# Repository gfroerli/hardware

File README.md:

## PCB

## Datasheets

- Enclosure: http://www.produktinfo.conrad.com/datenblaetter/525000-549999/536028-da-01-de-GEHAEUSE_ABS_PICCOLO_ABS_B_65_G.pdf

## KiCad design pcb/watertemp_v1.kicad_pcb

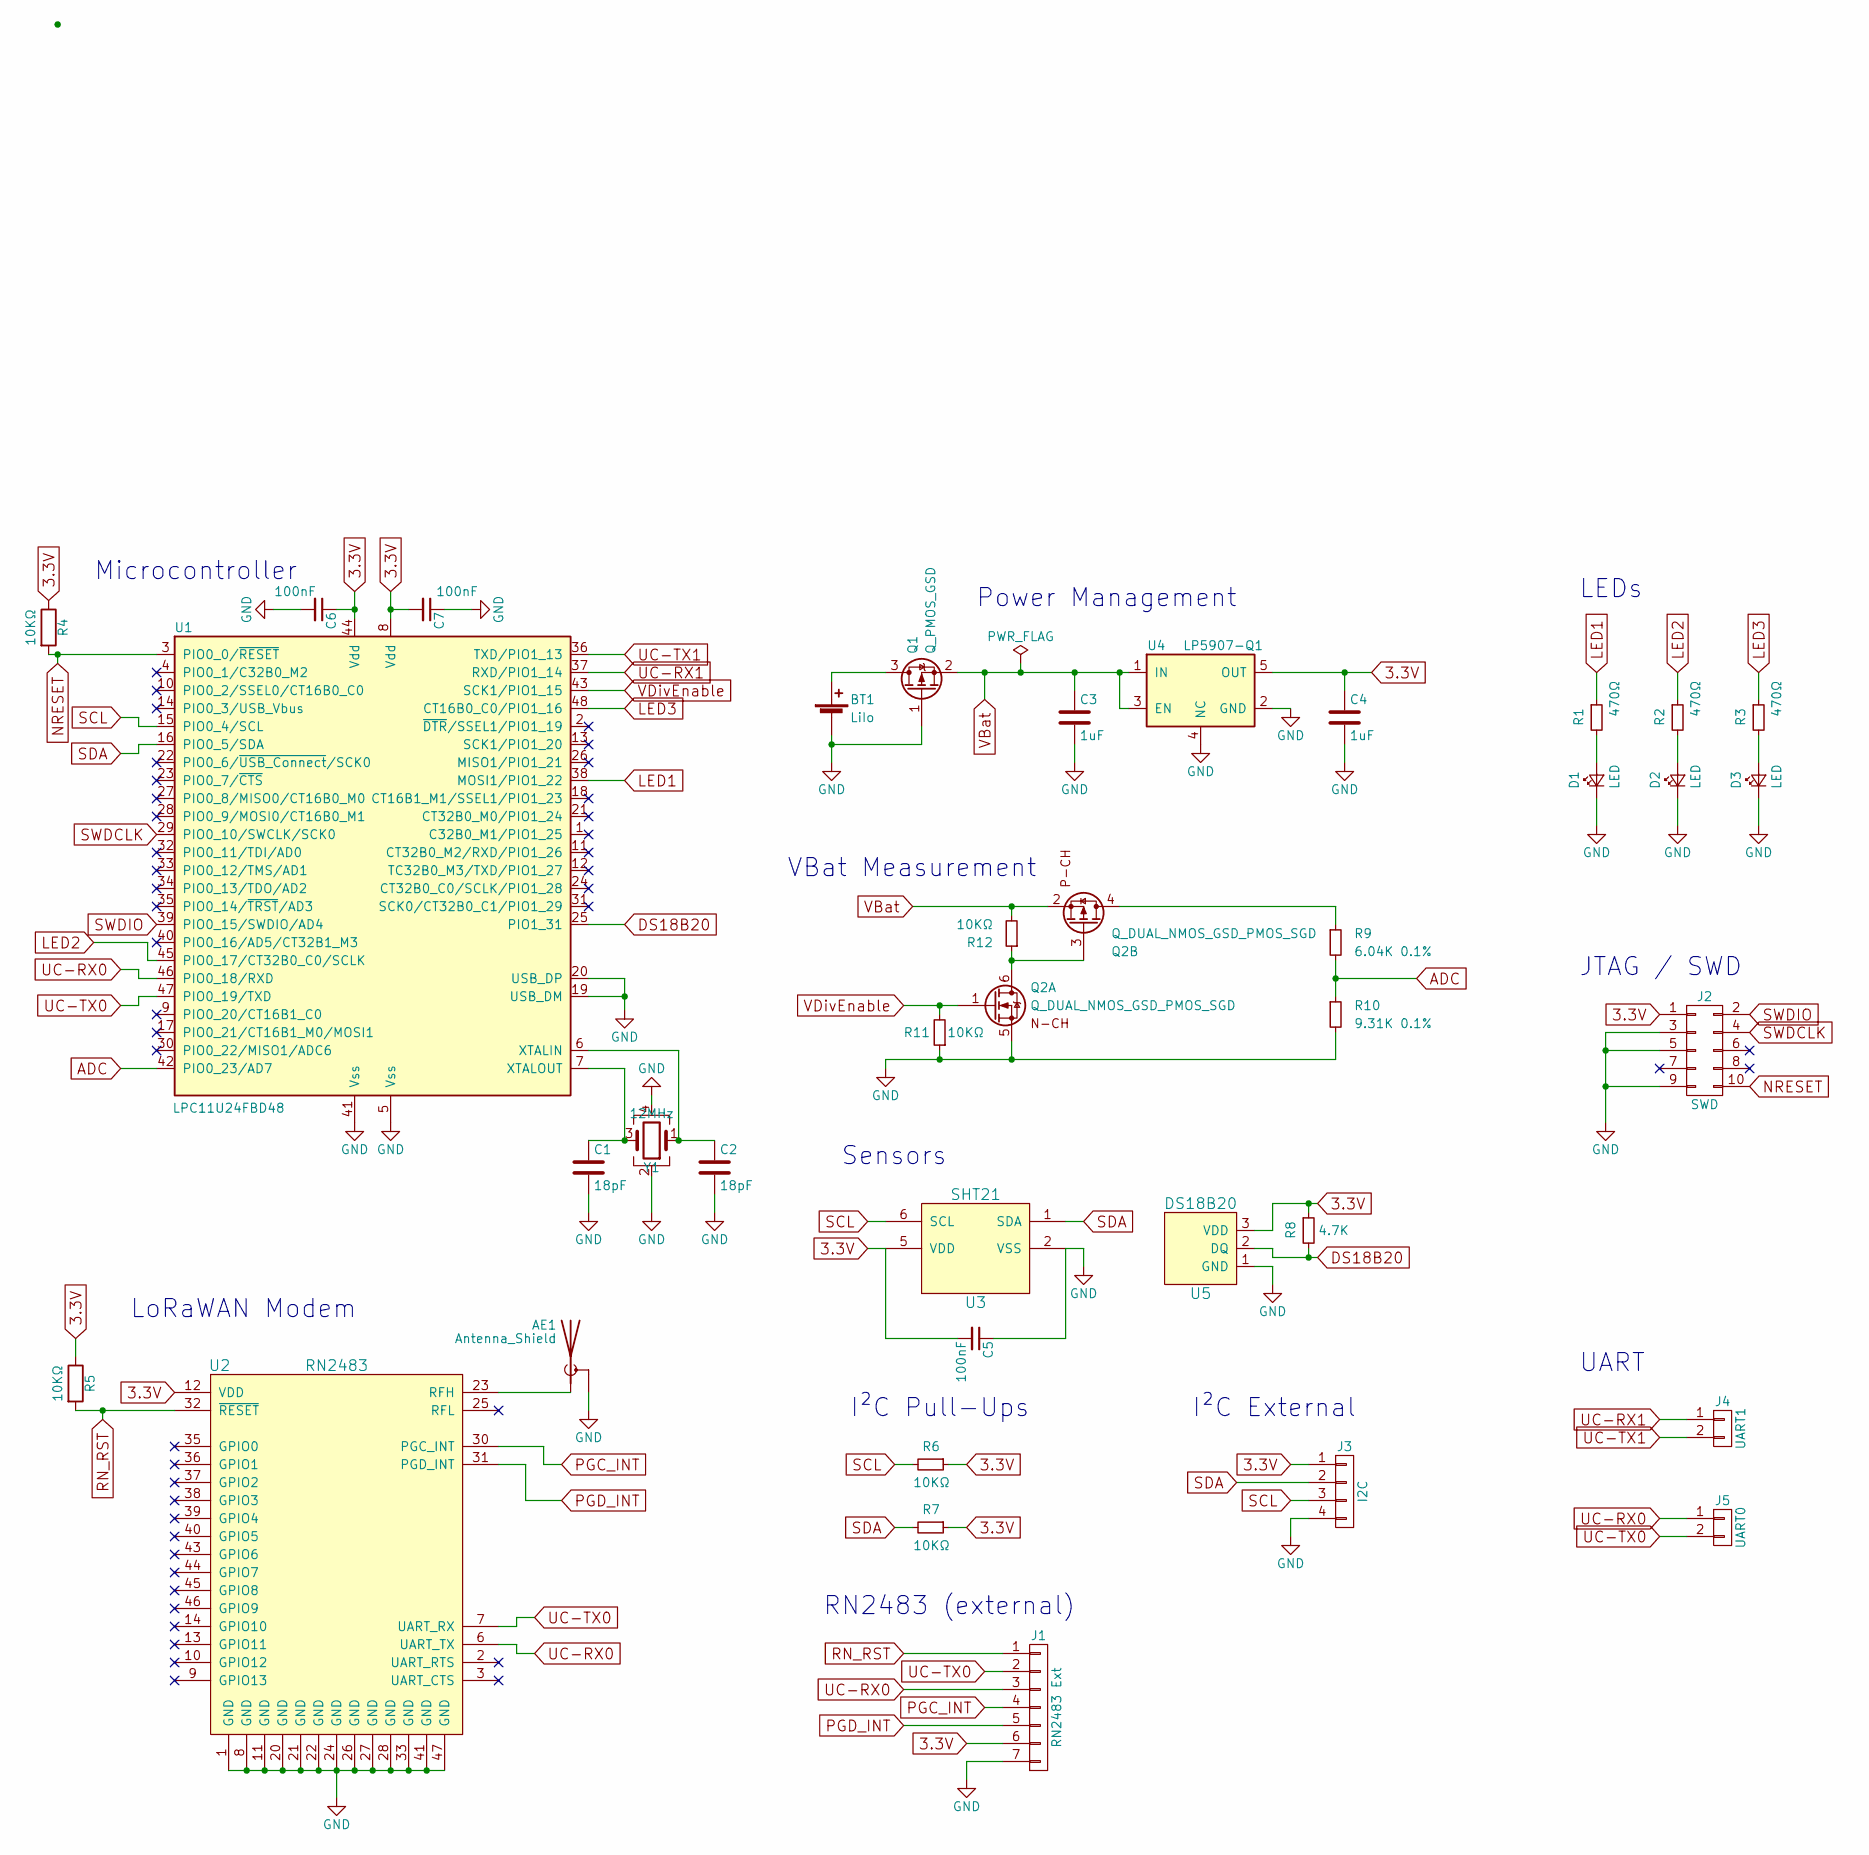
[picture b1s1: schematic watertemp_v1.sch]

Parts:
AE1: Antenna_Shield; SMA_EDGE; Digikey J502-ND
BT1: LiIo; 36-54-ND; Digikey 36-54-ND
C1, C2: 18pF; C_0805; Part Samsung CL21C180JBANNNC; Digikey 1276-1107-1-ND
C3: 1uF; C_0805; Part Samsung CL21B105KOFNNNG; Digikey 1276-6471-1-ND
C4: 1uF; C_0805; Part Samsung Samsung CL21B105KOFNNNG; Digikey 1276-6471-1-ND
C5: 100nF; C_0805_HandSoldering; Digikey 1276-6468-1-ND
C6, C7: 100nF; C_0805; Digikey 1276-6468-1-ND
D1: LED; LED_0805; Digikey 475-1278-1-ND
D2: LED; LED_0805; Digikey 475-2560-1-ND
D3: LED; LED_0805; Digikey 475-1410-1-ND
J1: RN2483 Ext; Pin_Header_Straight_1x07_Pitch2.54mm
J2: SWD; SWD_10Pin; Digikey 1175-1629-ND
J3: I2C; Pin_Header_Straight_1x04_Pitch2.54mm
J4: UART1; Pin_Header_Straight_1x02_Pitch2.54mm
J5: UART0; Pin_Header_Straight_1x02_Pitch2.54mm
Q1: Q_PMOS_GSD; SOT-23; Digikey SSM3J338RLFCT-ND
Q2: Q_DUAL_NMOS_GSD_PMOS_SGD; TSOT26; Digikey DMC2038LVT-7DICT-ND
R1, R2, R3: 470Ω; R_0805; Digikey 311-470CRCT-ND
R4, R5, R6, R7, R11, R12: 10KΩ; R_0805; Digikey 311-10KARCT-ND
R8: 4.7K; R_0805; Digikey 311-4.70KCRCT-ND
R9: 6.04K 0.1%; R_0805; Digikey P20683CT-ND
R10: 9.31K 0.1%; R_0805; Digikey YAG2002CT-ND
U1: LPC11U24FBD48; LQFP-48_7x7mm_Pitch0.5mm; Digikey 568-8460-ND
U2: RN2483; DigiKey RN2483A-I/RM103-ND
U3: SHT21
U4: LP5907-Q1; SOT-23-5; Digikey 296-40365-1-ND
U5: DS18B20; Pin_Header_Straight_1x03_Pitch2.54mm
Y1: 12MHz; Crystal_SMD_Abracon_ABM8G-4pin_3.2x2.5mm; Part ABM8G-12.000MHZ-4Y-T3; Digikey 535-10901-1-ND

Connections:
3.3V: C4.1, C5.2, C6.1, C7.2, J1.6, J2.1, J3.1, R4.1, R5.1, R6.1, R7.1, R8.1, U1.8 (Vdd), U1.44 (Vdd), U2.12 (VDD), U3.5 (VDD), U4.5 (OUT), U5.3 (VDD)
ADC: R9.2, R10.1, U1.42 (PIO0_23/AD7)
DS18B20: R8.2, U1.25 (PIO1_31), U5.2 (DQ)
GND: AE1.2 (Shield), BT1.2 (-), C1.2, C2.2, C3.2, C4.2, C5.1, C6.2, C7.1, D1.1 (K), D2.1 (K), D3.1 (K), J1.7, J2.3, J2.5, J2.9, J3.4, Q1.1 (G), Q2.5 (S1), R10.2, R11.1, U1.5 (Vss), U1.19 (USB_DM), U1.20 (USB_DP), U1.41 (Vss), U2.1 (GND), U2.8 (GND), U2.11 (GND), U2.20 (GND), U2.21 (GND), U2.22 (GND), U2.24 (GND), U2.26 (GND), U2.27 (GND), U2.28 (GND), U2.33 (GND), U2.41 (GND), U2.47 (GND), U3.2 (VSS), U4.2 (GND), U4.4 (NC), U5.1 (GND), Y1.2, Y1.4
LED1: R1.1, U1.38 (MOSI1/PIO1_22)
LED2: R2.1, U1.45 (PIO0_17/CT32B0_C0/SCLK)
LED3: R3.1, U1.48 (CT16B0_C0/PIO1_16)
NRESET: J2.10, R4.2, U1.3 (PIO0_0/~RESET)
unnamed: AE1.1 (A), U2.23 (RFH)
unnamed: BT1.1 (+), Q1.3 (D)
unnamed: C1.1, U1.7 (XTALOUT), Y1.3
unnamed: C2.1, U1.6 (XTALIN), Y1.1
unnamed: D1.2 (A), R1.2
unnamed: D2.2 (A), R2.2
unnamed: D3.2 (A), R3.2
unnamed: Q2.3 (G2), Q2.6 (D1), R12.1
unnamed: Q2.4 (D2), R9.1
PGC_INT: J1.4, U2.30 (PGC_INT)
PGD_INT: J1.5, U2.31 (PGD_INT)
RN_RST: J1.1, R5.2, U2.32 (~RESET)
SCL: J3.3, R6.2, U1.15 (PIO0_4/SCL), U3.6 (SCL)
SDA: J3.2, R7.2, U1.16 (PIO0_5/SDA), U3.1 (SDA)
SWDCLK: J2.4, U1.29 (PIO0_10/SWCLK/SCK0)
SWDIO: J2.2, U1.39 (PIO0_15/SWDIO/AD4)
UC-RX0: J1.3, J5.1, U1.46 (PIO0_18/RXD), U2.6 (UART_TX)
UC-RX1: J4.1, U1.37 (RXD/PIO1_14)
UC-TX0: J1.2, J5.2, U1.47 (PIO0_19/TXD), U2.7 (UART_RX)
UC-TX1: J4.2, U1.36 (TXD/PIO1_13)
VBat: C3.1, Q1.2 (S), Q2.2 (S2), R12.2, U4.1 (IN), U4.3 (EN)
VDivEnable: Q2.1 (G1), R11.2, U1.43 (SCK1/PIO1_15)

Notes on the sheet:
Power Management
Microcontroller
LoRaWAN Modem
Sensors
JTAG / SWD
LEDs
I²C Pull-Ups
I²C External
UART
RN2483 (external)
VBat Measurement

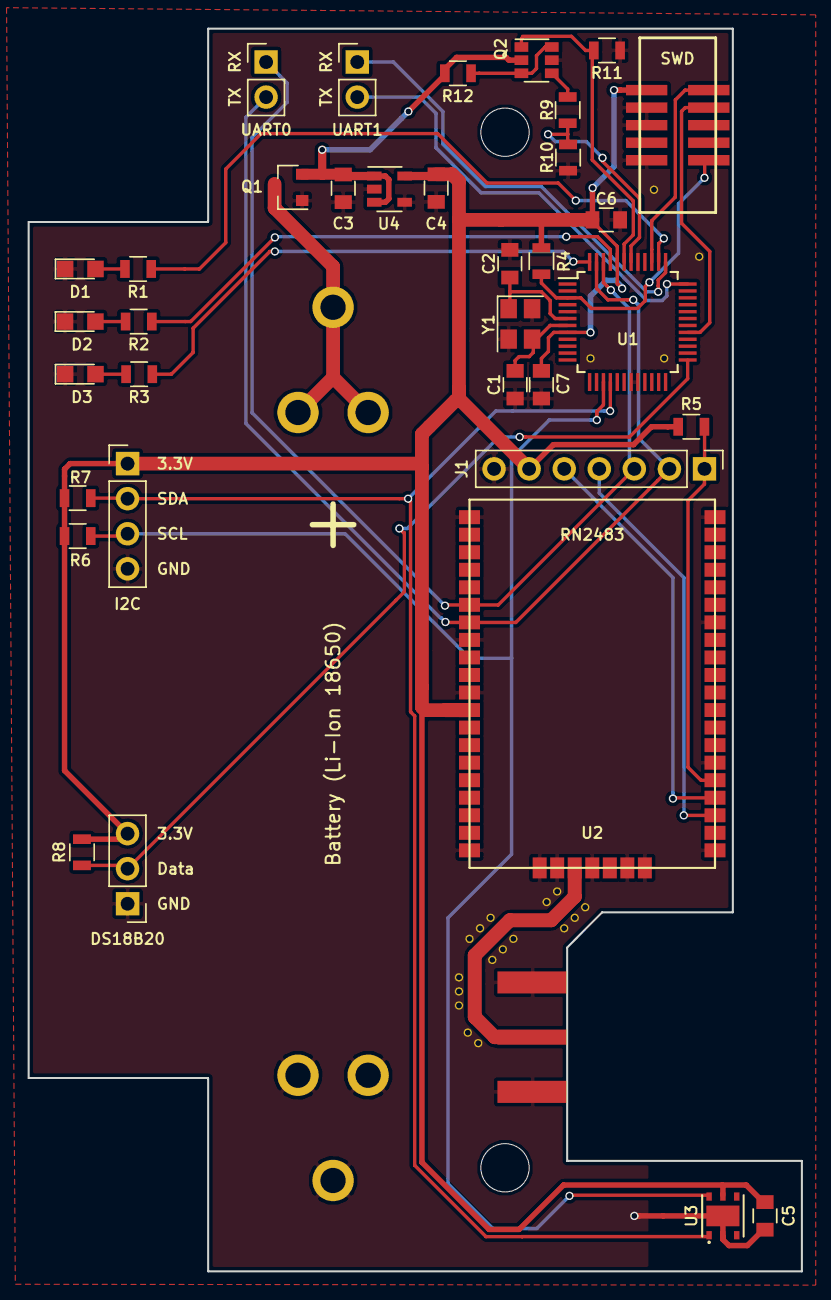
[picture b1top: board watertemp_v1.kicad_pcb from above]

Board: 2 copper layers, 56.0 x 90.0 mm, 37 parts (0 on the bottom side), 30 nets.

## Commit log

2017-06-21 Import from coredump-ch/watertemp repo
2017-06-21 Start BOM
2017-07-22 Add LEDs
2017-07-22 Add I²C connector and pull-ups
2017-07-22 Add UART debug pins
2017-07-22 Add connector for external RN2483 board
2017-07-22 Expose RN2483 ICSP header
2017-07-22 Reorganize schematics
2017-07-22 Export netlist
2017-07-24 Finish parts selection
    - Replace 20 pin JTAG connector with 10 pin SWD connector
    - Choose footprints for all parts
2017-07-24 Expose both UARTs
2017-08-15 Continue work on PCB
2017-08-15 Finish routing first version
2017-08-15 Some more details
2017-08-16 Enlarge some of the pads for hand soldering
2017-08-16 Add OSHW and Coredump logos (fixes #5)
2017-08-21 Add LDO Digikey part number
2017-09-18 Add reverse polarity protection (fixes #11)
2017-09-18 Add more stitching vias (fixes #6)
2017-09-18 Fix oscillator symbol/footprint (fixes #10)
2017-09-18 Move oscillator closer µC
2017-10-05 Add silkscreen labels to UART headers (fixes #1)
2017-10-05 Make SWD footprint pads larger (fixes #2)
2017-10-05 Fix problems with LDO
    - Use SOT-23-5 footprint (fixes #9)
    - Connect EN to IN
    - Connect pin 4 (NC) to GND as recommended in the
    datasheet (section 11.2)
2017-11-06 Add draft of voltage divider (refs #4)
2017-11-06 Connect USB_DM/DP pins to GND
    According to datasheet:
    > If the pins are not used, tie floating pi ns to ground or power to
    > minimize power consumption.
2017-11-06 Connect battery meter to µC
2017-11-06 Fix stuff by Raphi :D
2017-11-06 Add TSOT26 footprint and regenerate netlist
2017-11-07 Routing for voltage divider (fixes #4)
2017-11-07 Increase 3.3 supply line thickness
2017-11-07 Connect remaining unconnected parts
2017-11-08 Nicer routing of traces
2017-11-08 More routing and silkscreen optimizations
2017-11-13 Add Digikey part number to RN248
2017-11-13 Add order numbers to schema elements
2017-11-18 Improve fabrication layer
2017-11-20 Add BOM table
2017-11-20 Expand BOM with manufacturer no and designators
2017-11-21 Update PCB photo
2017-11-26 Improve R6/R7 placing
2017-12-05 Add schematics PDF
